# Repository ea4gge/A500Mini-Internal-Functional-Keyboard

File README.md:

# The A500Mini AmigaWave and RetroWiki's Internal Functional Keyboard Project

<br>

<br>

This is project of the A500Mini internal functional keyboard, based in 32U4 processor (Arduino leonardo, for example).

Actually it is working as final release, feel free to use, modify, recreate, ...

<br>

<br>

<br>

<br>

<br>

<br>

<br>

<br>

# The features:

1.- HID internal fully functional keyboard, with F12 key in the "eject" button of the disk drive, CAPS Lock led, ...

2.- Internal 4 USB's HUB: One for the keyboard, one for the SD reader, one internal free (for network, for example) tha last one for the rear original placed USB on the main unit (because one of the original populated USB must be used por the hub's imput)

3.- SD card's reader exactly in the floppy disk's place.

4.- A lot of smiles after the fabrication :D 

The readme file and the help file for the fabrication is WIP at the moment.

All the mechanical procedures are made by Kikems_Retro.

The presentation of the first prototype  (one weekend JOB) was in the youtube's AmigaWave program. We have also presented in the "Posadas party", in Spain 

The inspiration for my own code was from the "Armapad36v2" because is my firstt program of an USB Keyboard. Many thanks for the Author of this!!!

Spetial thanks to EA4EOZ. He has had the idea of use the Eject button and gave me a lot of help in the code of the Arduino

<br>

<br>

<br>

<br>

Many thanks to all and Enjoy!!

Lince// EA4GGE

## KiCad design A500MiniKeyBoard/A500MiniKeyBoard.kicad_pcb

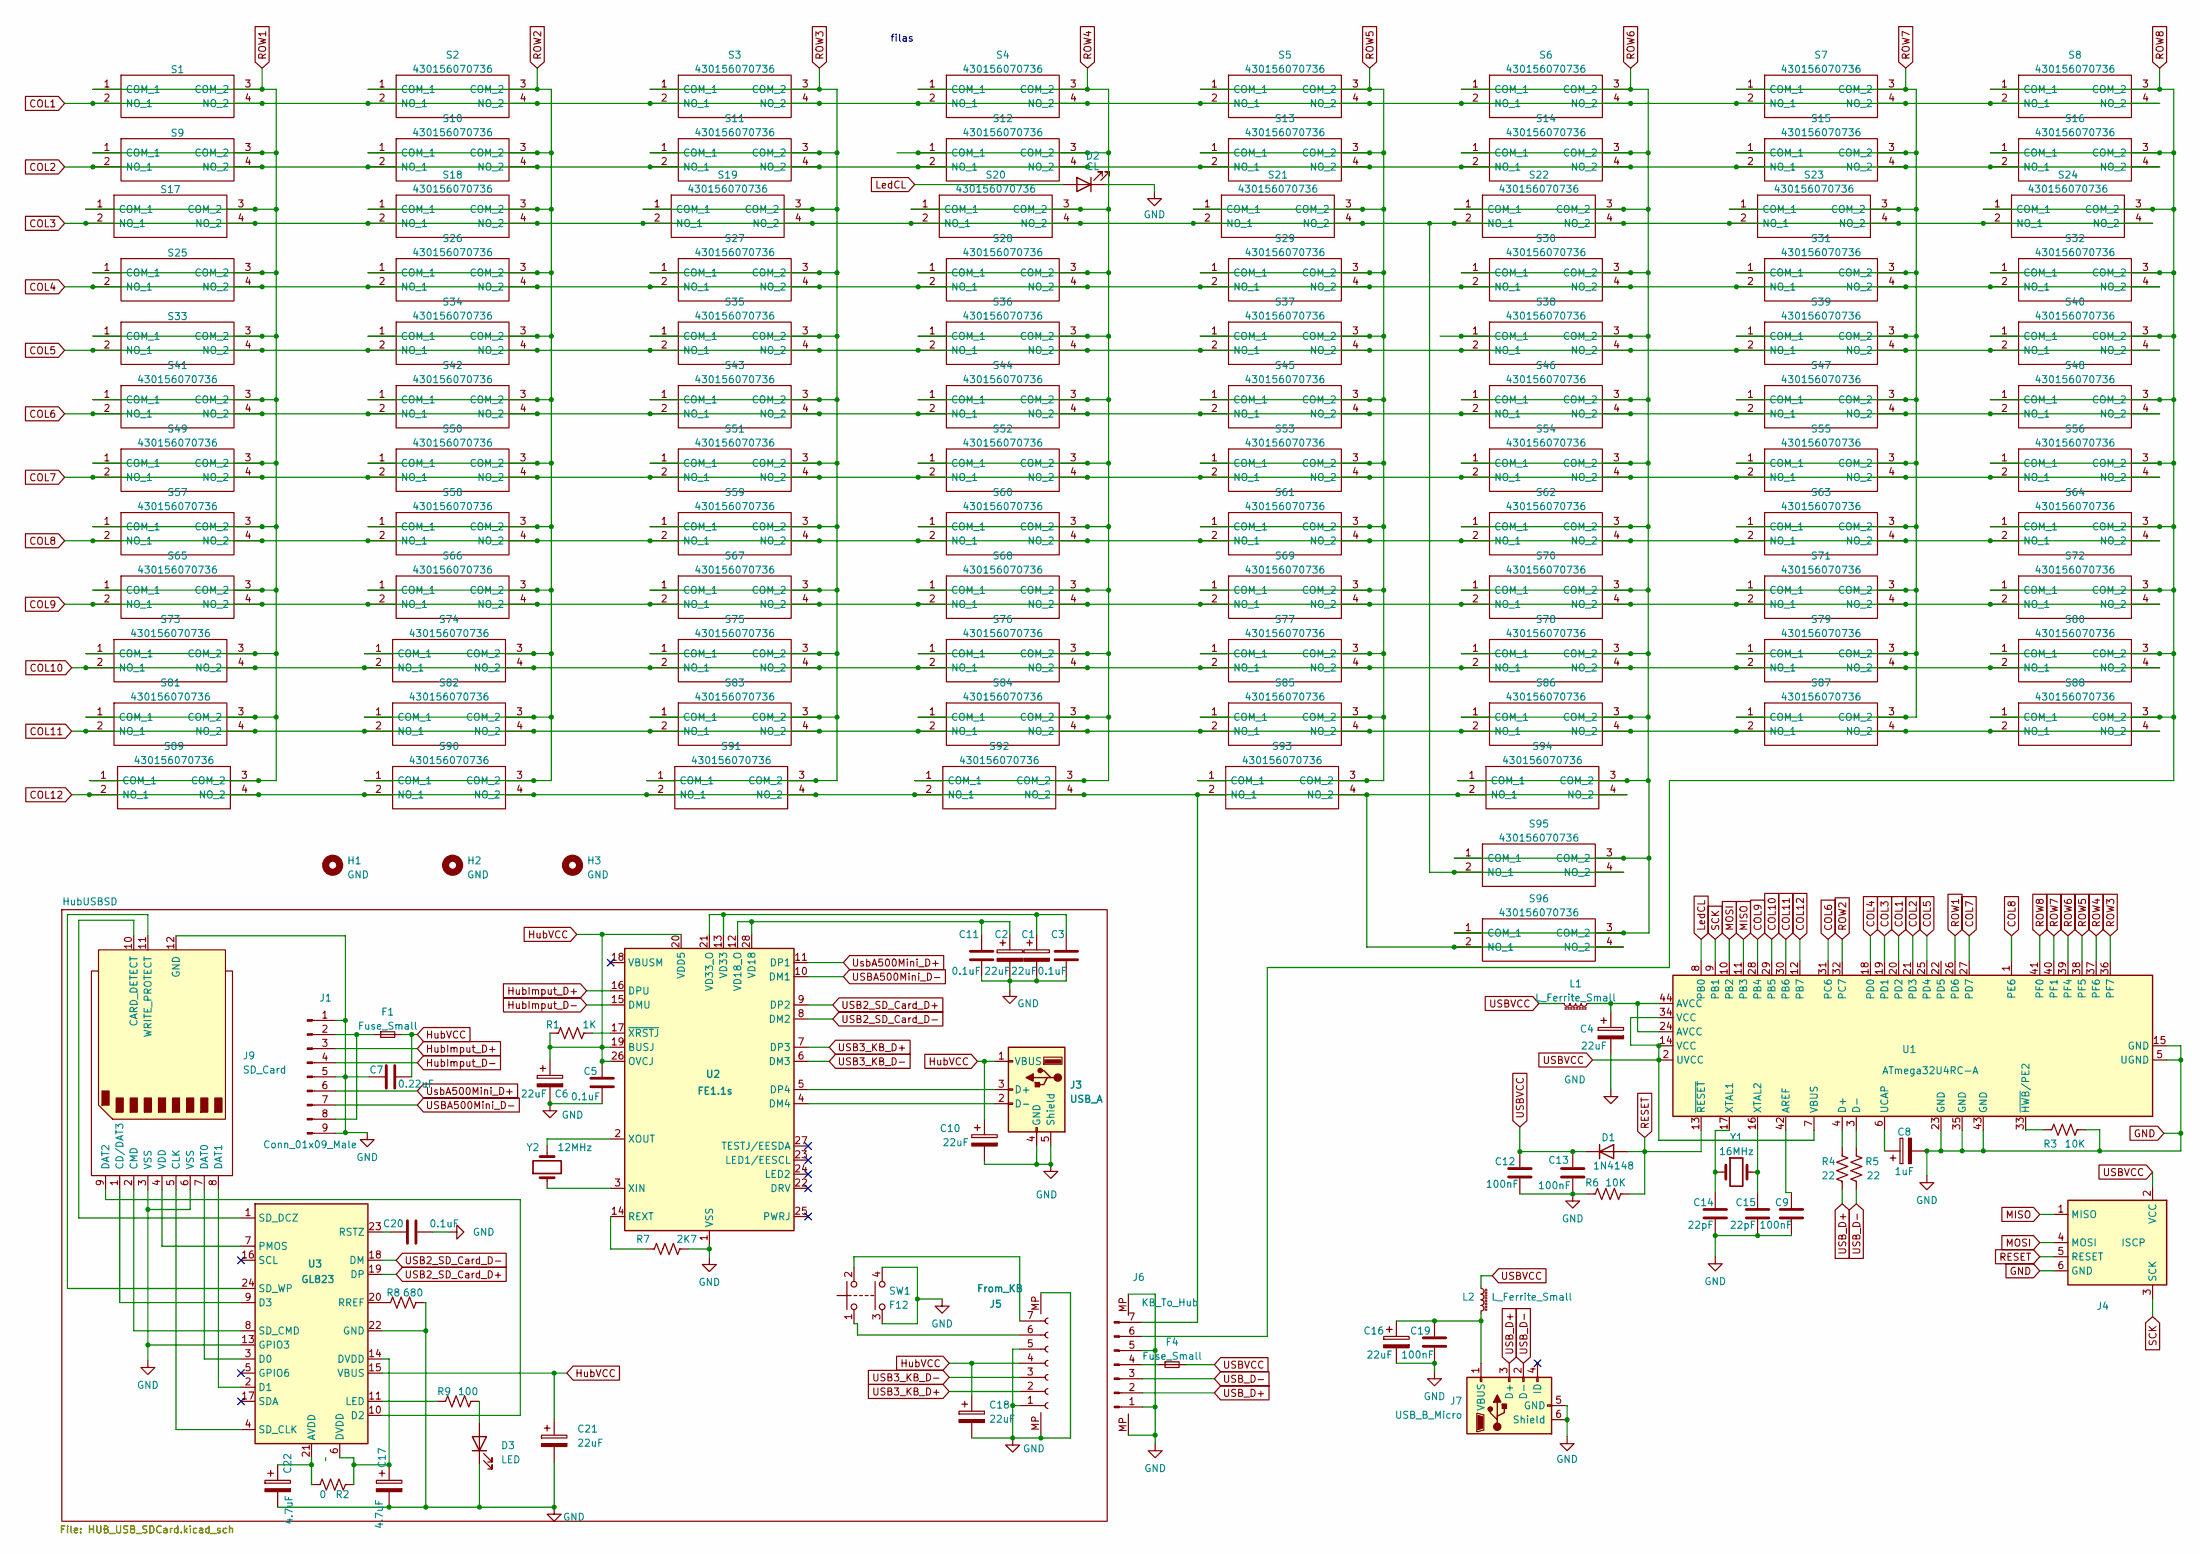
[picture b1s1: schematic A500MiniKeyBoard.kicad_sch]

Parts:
C1, C2, C4, C6, C10, C16, C18, C21: 22uF; CP_EIA-3528-21_Kemet-B_Pad1.50x2.35mm_HandSolder
C3, C5, C11, C20: 0.1uF; C_0805_2012Metric_Pad1.18x1.45mm_HandSolder
C7: 0.22uF; C_0805_2012Metric_Pad1.18x1.45mm_HandSolder
C8: 1uF; CP_EIA-3528-21_Kemet-B_Pad1.50x2.35mm_HandSolder
C9, C12, C13, C19: 100nF; C_0805_2012Metric_Pad1.18x1.45mm_HandSolder
C14, C15: 22pF; C_0805_2012Metric_Pad1.18x1.45mm_HandSolder
C17, C22: 4.7uF; CP_EIA-3528-21_Kemet-B_Pad1.50x2.35mm_HandSolder
D1: 1N4148; D_0805_2012Metric_Pad1.15x1.40mm_HandSolder
D2: CL; LED_0603_1608Metric
D3: LED; LED_D3.0mm_Horizontal_O1.27mm_Z2.0mm
F1, F4: Fuse_Small; Fuse_2920_7451Metric_Pad2.10x5.45mm_HandSolder
H1, H2, H3: GND; MountingHole_2.1mm
J1: Conn_01x09_Male; PinHeader_1x09_P2.54mm_Horizontal
J3: USB_A; USB_A_Molex_67643_Horizontal
J4: ISCP; PinHeader_2x03_P2.54mm_Vertical
J5: From_KB; TE_84953-7_1x07-1MP_P1.0mm_Horizontal
J6: KB_To_Hub; TE_84953-7_1x07-1MP_P1.0mm_Horizontal
J7: USB_B_Micro; USB_Micro-B_Amphenol_10118194_Horizontal
J9: SD_Card; SD_TE_2041021
L1, L2: L_Ferrite_Small; L_0805_2012Metric_Pad1.05x1.20mm_HandSolder
R1: 1K; R_0805_2012Metric_Pad1.20x1.40mm_HandSolder
R2: 0; R_0805_2012Metric_Pad1.20x1.40mm_HandSolder
R3, R6: 10K; R_0805_2012Metric_Pad1.20x1.40mm_HandSolder
R4, R5: 22; R_0805_2012Metric_Pad1.20x1.40mm_HandSolder
R7: 2K7; R_0805_2012Metric_Pad1.20x1.40mm_HandSolder
R8: 680; R_0805_2012Metric_Pad1.20x1.40mm_HandSolder
R9: 100; R_0805_2012Metric_Pad1.20x1.40mm_HandSolder
S1, S2, S3, S4, S5, S6, S7, S8, S9, S10, S11, S12, S13, S14, S15, S16, S17, S18, S19, S20, S21, S22, S23, S24, S25, S26, S27, S28, S29, S30, S31, S32, S33, S34, S35, S36, S37, S38, S39, S40, S41, S42, S43, S44, S45, S46, S47, S48, S49, S50, S51, S52, S53, S54, S55, S56, S57, S58, S59, S60, S61, S62, S63, S64, S65, S66, S67, S68, S69, S70, S71, S72, S73, S74, S75, S76, S77, S78, S79, S80, S81, S82, S83, S84, S85, S86, S87, S88, S89, S90, S91, S92, S93, S94, S95, S96: 430156070736; SW_PUSH_6mm_H7.3mm_mia; Mouser Part Number N/A
SW1: F12; SW_Tactile_SPST_Angled_PTS645Vx83-2LFS
U1: ATmega32U4RC-A; TQFP-44_10x10mm_P0.8mm
U2: FE1.1s; SSOP-28_3.9x9.9mm_P0.635mm
U3: GL823; SSOP-24_3.9x8.7mm_P0.635mm
Y1: 16MHz; Crystal_HC49-4H_Vertical
Y2: 12MHz; Crystal_HC49-4H_Vertical

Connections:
COL1: S1.2 (NO_1), S1.4 (NO_2), S2.2 (NO_1), S2.4 (NO_2), S3.2 (NO_1), S3.4 (NO_2), S4.2 (NO_1), S4.4 (NO_2), S5.2 (NO_1), S5.4 (NO_2), S6.2 (NO_1), S6.4 (NO_2), S7.2 (NO_1), S7.4 (NO_2), S8.2 (NO_1), S8.4 (NO_2), U1.20 (PD2)
COL2: S9.2 (NO_1), S9.4 (NO_2), S10.2 (NO_1), S10.4 (NO_2), S11.2 (NO_1), S11.4 (NO_2), S12.2 (NO_1), S12.4 (NO_2), S13.2 (NO_1), S13.4 (NO_2), S14.2 (NO_1), S14.4 (NO_2), S15.2 (NO_1), S15.4 (NO_2), S16.2 (NO_1), S16.4 (NO_2), U1.21 (PD3)
COL3: S17.2 (NO_1), S17.4 (NO_2), S18.2 (NO_1), S18.4 (NO_2), S19.2 (NO_1), S19.4 (NO_2), S20.2 (NO_1), S20.4 (NO_2), S21.2 (NO_1), S21.4 (NO_2), S22.2 (NO_1), S22.4 (NO_2), S23.2 (NO_1), S23.4 (NO_2), S24.2 (NO_1), S24.4 (NO_2), S95.2 (NO_1), S95.4 (NO_2), U1.19 (PD1)
COL4: S25.2 (NO_1), S25.4 (NO_2), S26.2 (NO_1), S26.4 (NO_2), S27.2 (NO_1), S27.4 (NO_2), S28.2 (NO_1), S28.4 (NO_2), S29.2 (NO_1), S29.4 (NO_2), S30.2 (NO_1), S30.4 (NO_2), S31.2 (NO_1), S31.4 (NO_2), S32.2 (NO_1), S32.4 (NO_2), U1.18 (PD0)
COL5: S33.2 (NO_1), S33.4 (NO_2), S34.2 (NO_1), S34.4 (NO_2), S35.2 (NO_1), S35.4 (NO_2), S36.2 (NO_1), S36.4 (NO_2), S37.2 (NO_1), S37.4 (NO_2), S38.2 (NO_1), S38.4 (NO_2), S39.2 (NO_1), S39.4 (NO_2), S40.2 (NO_1), S40.4 (NO_2), U1.25 (PD4)
COL6: S41.2 (NO_1), S41.4 (NO_2), S42.2 (NO_1), S42.4 (NO_2), S43.2 (NO_1), S43.4 (NO_2), S44.2 (NO_1), S44.4 (NO_2), S45.2 (NO_1), S45.4 (NO_2), S46.2 (NO_1), S46.4 (NO_2), S47.2 (NO_1), S47.4 (NO_2), S48.2 (NO_1), S48.4 (NO_2), U1.31 (PC6)
COL7: S49.2 (NO_1), S49.4 (NO_2), S50.2 (NO_1), S50.4 (NO_2), S51.2 (NO_1), S51.4 (NO_2), S52.2 (NO_1), S52.4 (NO_2), S53.2 (NO_1), S53.4 (NO_2), S54.2 (NO_1), S54.4 (NO_2), S55.2 (NO_1), S55.4 (NO_2), S56.2 (NO_1), S56.4 (NO_2), U1.27 (PD7)
COL8: S57.2 (NO_1), S57.4 (NO_2), S58.2 (NO_1), S58.4 (NO_2), S59.2 (NO_1), S59.4 (NO_2), S60.2 (NO_1), S60.4 (NO_2), S61.2 (NO_1), S61.4 (NO_2), S62.2 (NO_1), S62.4 (NO_2), S63.2 (NO_1), S63.4 (NO_2), S64.2 (NO_1), S64.4 (NO_2), U1.1 (PE6)
COL9: S65.2 (NO_1), S65.4 (NO_2), S66.2 (NO_1), S66.4 (NO_2), S67.2 (NO_1), S67.4 (NO_2), S68.2 (NO_1), S68.4 (NO_2), S69.2 (NO_1), S69.4 (NO_2), S70.2 (NO_1), S70.4 (NO_2), S71.2 (NO_1), S71.4 (NO_2), S72.2 (NO_1), S72.4 (NO_2), U1.28 (PB4)
COL10: S73.2 (NO_1), S73.4 (NO_2), S74.2 (NO_1), S74.4 (NO_2), S75.2 (NO_1), S75.4 (NO_2), S76.2 (NO_1), S76.4 (NO_2), S77.2 (NO_1), S77.4 (NO_2), S78.2 (NO_1), S78.4 (NO_2), S79.2 (NO_1), S79.4 (NO_2), S80.2 (NO_1), S80.4 (NO_2), U1.29 (PB5)
COL11: S81.2 (NO_1), S81.4 (NO_2), S82.2 (NO_1), S82.4 (NO_2), S83.2 (NO_1), S83.4 (NO_2), S84.2 (NO_1), S84.4 (NO_2), S85.2 (NO_1), S85.4 (NO_2), S86.2 (NO_1), S86.4 (NO_2), S87.2 (NO_1), S87.4 (NO_2), S88.2 (NO_1), S88.4 (NO_2), U1.30 (PB6)
COL12: J6.7, S89.2 (NO_1), S89.4 (NO_2), S90.2 (NO_1), S90.4 (NO_2), S91.2 (NO_1), S91.4 (NO_2), S92.2 (NO_1), S92.4 (NO_2), S93.2 (NO_1), S93.4 (NO_2), S94.2 (NO_1), S94.4 (NO_2), S96.2 (NO_1), S96.4 (NO_2), U1.12 (PB7)
GND: C1.2, C2.2, C3.1, C4.2, C5.1, C6.2, C7.1, C8.2, C9.2, C10.2, C11.2, C12.1, C13.1, C14.2, C15.2, C16.2, C17.2, C18.2, C19.1, C20.1, C21.2, C22.2, D2.1 (K), D3.1 (K), J1.1, J1.5, J1.9, J3.4 (GND), J3.5 (Shield), J4.6 (GND), J5.1, J5.5, J5.MP, J6.1, J6.5, J6.MP, J7.5 (GND), J7.6 (Shield), J9.3 (VSS), J9.6 (VSS), J9.12 (GND), R3.2, R6.1, R7.1, R8.1, SW1.3, SW1.4, U1.5 (UGND), U1.15 (GND), U1.23 (GND), U1.35 (GND), U1.43 (GND), U2.1 (VSS), U3.13 (GPIO3), U3.22 (GND)
HubImput_D+: J1.3, U2.16 (DPU)
HubImput_D-: J1.4, U2.15 (DMU)
HubVCC: C5.2, C6.1, C7.2, C10.1, C18.1, C21.1, F1.2, J3.1 (VBUS), J5.4, R1.2, U2.19 (BUSJ), U2.20 (VDD5), U2.26 (OVCJ), U3.15 (VBUS)
LedCL: D2.2 (A), U1.8 (PB0)
MISO: J4.1 (MISO), U1.11 (PB3)
MOSI: J4.4 (MOSI), U1.10 (PB2)
unnamed: C4.1, L1.1, U1.24 (AVCC), U1.44 (AVCC)
unnamed: C17.1, R2.2, U3.6 (DVDD), U3.14 (DVDD)
unnamed: D3.2 (A), R9.1
unnamed: F1.1, J1.2, J1.8
unnamed: J3.3 (D+), U2.5 (DP4)
unnamed: J3.2 (D-), U2.4 (DM4)
unnamed: J5.6, SW1.1
unnamed: J5.7, SW1.2
unnamed: F4.1, J6.4
unnamed: C16.1, C19.2, J7.1 (VBUS), L2.2
unnamed: J9.10 (CARD_DETECT), U3.1 (SD_DCZ)
unnamed: J9.1 (CD/DAT3), U3.9 (D3)
unnamed: J9.5 (CLK), U3.4 (SD_CLK)
unnamed: J9.2 (CMD), U3.8 (SD_CMD)
unnamed: J9.7 (DAT0), U3.3 (D0)
unnamed: J9.8 (DAT1), U3.2 (D1)
unnamed: J9.9 (DAT2), U3.10 (D2)
unnamed: J9.4 (VDD), U3.7 (PMOS)
unnamed: J9.11 (WRITE_PROTECT), U3.24 (SD_WP)
unnamed: C9.1, U1.42 (AREF)
unnamed: R4.1, U1.4 (D+)
unnamed: R5.1, U1.3 (D-)
unnamed: C8.1, U1.6 (UCAP)
unnamed: C14.1, U1.17 (XTAL1), Y1.1
unnamed: C15.1, U1.16 (XTAL2), Y1.2
unnamed: R3.1, U1.33 (~HWB/PE2)
unnamed: R7.2, U2.14 (REXT)
unnamed: C2.1, C11.1, U2.12 (VD18_O), U2.28 (VD18)
unnamed: C1.1, C3.2, U2.13 (VD33), U2.21 (VD33_O)
unnamed: U2.3 (XIN), Y2.1
unnamed: U2.2 (XOUT), Y2.2
unnamed: R1.1, U2.17 (~XRSTJ)
unnamed: C22.1, R2.1, U3.21 (AVDD)
unnamed: R9.2, U3.11 (LED)
unnamed: R8.2, U3.20 (RREF)
unnamed: C20.2, U3.23 (RSTZ)
RESET: D1.2 (A), J4.5 (RESET), R6.2, U1.13 (~RESET)
ROW1: S1.1 (COM_1), S1.3 (COM_2), S9.1 (COM_1), S9.3 (COM_2), S17.1 (COM_1), S17.3 (COM_2), S25.1 (COM_1), S25.3 (COM_2), S33.1 (COM_1), S33.3 (COM_2), S41.1 (COM_1), S41.3 (COM_2), S49.1 (COM_1), S49.3 (COM_2), S57.1 (COM_1), S57.3 (COM_2), S65.1 (COM_1), S65.3 (COM_2), S73.1 (COM_1), S73.3 (COM_2), S81.1 (COM_1), S81.3 (COM_2), S89.1 (COM_1), S89.3 (COM_2), U1.26 (PD6)
ROW2: S2.1 (COM_1), S2.3 (COM_2), S10.1 (COM_1), S10.3 (COM_2), S18.1 (COM_1), S18.3 (COM_2), S26.1 (COM_1), S26.3 (COM_2), S34.1 (COM_1), S34.3 (COM_2), S42.1 (COM_1), S42.3 (COM_2), S50.1 (COM_1), S50.3 (COM_2), S58.1 (COM_1), S58.3 (COM_2), S66.1 (COM_1), S66.3 (COM_2), S74.1 (COM_1), S74.3 (COM_2), S82.1 (COM_1), S82.3 (COM_2), S90.1 (COM_1), S90.3 (COM_2), U1.32 (PC7)
ROW3: S3.1 (COM_1), S3.3 (COM_2), S11.1 (COM_1), S11.3 (COM_2), S19.1 (COM_1), S19.3 (COM_2), S27.1 (COM_1), S27.3 (COM_2), S35.1 (COM_1), S35.3 (COM_2), S43.1 (COM_1), S43.3 (COM_2), S51.1 (COM_1), S51.3 (COM_2), S59.1 (COM_1), S59.3 (COM_2), S67.1 (COM_1), S67.3 (COM_2), S75.1 (COM_1), S75.3 (COM_2), S83.1 (COM_1), S83.3 (COM_2), S91.1 (COM_1), S91.3 (COM_2), U1.36 (PF7)
ROW4: S4.1 (COM_1), S4.3 (COM_2), S12.1 (COM_1), S12.3 (COM_2), S20.1 (COM_1), S20.3 (COM_2), S28.1 (COM_1), S28.3 (COM_2), S36.1 (COM_1), S36.3 (COM_2), S44.1 (COM_1), S44.3 (COM_2), S52.1 (COM_1), S52.3 (COM_2), S60.1 (COM_1), S60.3 (COM_2), S68.1 (COM_1), S68.3 (COM_2), S76.1 (COM_1), S76.3 (COM_2), S84.1 (COM_1), S84.3 (COM_2), S92.1 (COM_1), S92.3 (COM_2), U1.37 (PF6)
ROW5: S5.1 (COM_1), S5.3 (COM_2), S13.1 (COM_1), S13.3 (COM_2), S21.1 (COM_1), S21.3 (COM_2), S29.1 (COM_1), S29.3 (COM_2), S37.1 (COM_1), S37.3 (COM_2), S45.1 (COM_1), S45.3 (COM_2), S53.1 (COM_1), S53.3 (COM_2), S61.1 (COM_1), S61.3 (COM_2), S69.1 (COM_1), S69.3 (COM_2), S77.1 (COM_1), S77.3 (COM_2), S85.1 (COM_1), S85.3 (COM_2), S93.1 (COM_1), S93.3 (COM_2), U1.38 (PF5)
ROW6: S6.1 (COM_1), S6.3 (COM_2), S14.1 (COM_1), S14.3 (COM_2), S22.1 (COM_1), S22.3 (COM_2), S30.1 (COM_1), S30.3 (COM_2), S38.1 (COM_1), S38.3 (COM_2), S46.1 (COM_1), S46.3 (COM_2), S54.1 (COM_1), S54.3 (COM_2), S62.1 (COM_1), S62.3 (COM_2), S70.1 (COM_1), S70.3 (COM_2), S78.1 (COM_1), S78.3 (COM_2), S86.1 (COM_1), S86.3 (COM_2), S94.1 (COM_1), S94.3 (COM_2), S95.1 (COM_1), S95.3 (COM_2), S96.1 (COM_1), S96.3 (COM_2), U1.39 (PF4)
ROW7: S7.1 (COM_1), S7.3 (COM_2), S15.1 (COM_1), S15.3 (COM_2), S23.1 (COM_1), S23.3 (COM_2), S31.1 (COM_1), S31.3 (COM_2), S39.1 (COM_1), S39.3 (COM_2), S47.1 (COM_1), S47.3 (COM_2), S55.1 (COM_1), S55.3 (COM_2), S63.1 (COM_1), S63.3 (COM_2), S71.1 (COM_1), S71.3 (COM_2), S79.1 (COM_1), S79.3 (COM_2), S87.1 (COM_1), S87.3 (COM_2), U1.40 (PF1)
ROW8: J6.6, S8.1 (COM_1), S8.3 (COM_2), S16.1 (COM_1), S16.3 (COM_2), S24.1 (COM_1), S24.3 (COM_2), S32.1 (COM_1), S32.3 (COM_2), S40.1 (COM_1), S40.3 (COM_2), S48.1 (COM_1), S48.3 (COM_2), S56.1 (COM_1), S56.3 (COM_2), S64.1 (COM_1), S64.3 (COM_2), S72.1 (COM_1), S72.3 (COM_2), S80.1 (COM_1), S80.3 (COM_2), S88.1 (COM_1), S88.3 (COM_2), U1.41 (PF0)
SCK: J4.3 (SCK), U1.9 (PB1)
USB2_SD_Card_D+: U2.9 (DP2), U3.19 (DP)
USB2_SD_Card_D-: U2.8 (DM2), U3.18 (DM)
USB3_KB_D+: J5.2, U2.7 (DP3)
USB3_KB_D-: J5.3, U2.6 (DM3)
USBA500Mini_D-: J1.7, U2.10 (DM1)
USBVCC: C12.2, C13.2, D1.1 (K), F4.2, J4.2 (VCC), L1.2, L2.1, U1.2 (UVCC), U1.7 (VBUS), U1.14 (VCC), U1.34 (VCC)
USB_D+: J6.2, J7.3 (D+), R4.2
USB_D-: J6.3, J7.2 (D-), R5.2
UsbA500Mini_D+: J1.6, U2.11 (DP1)

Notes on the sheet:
filas

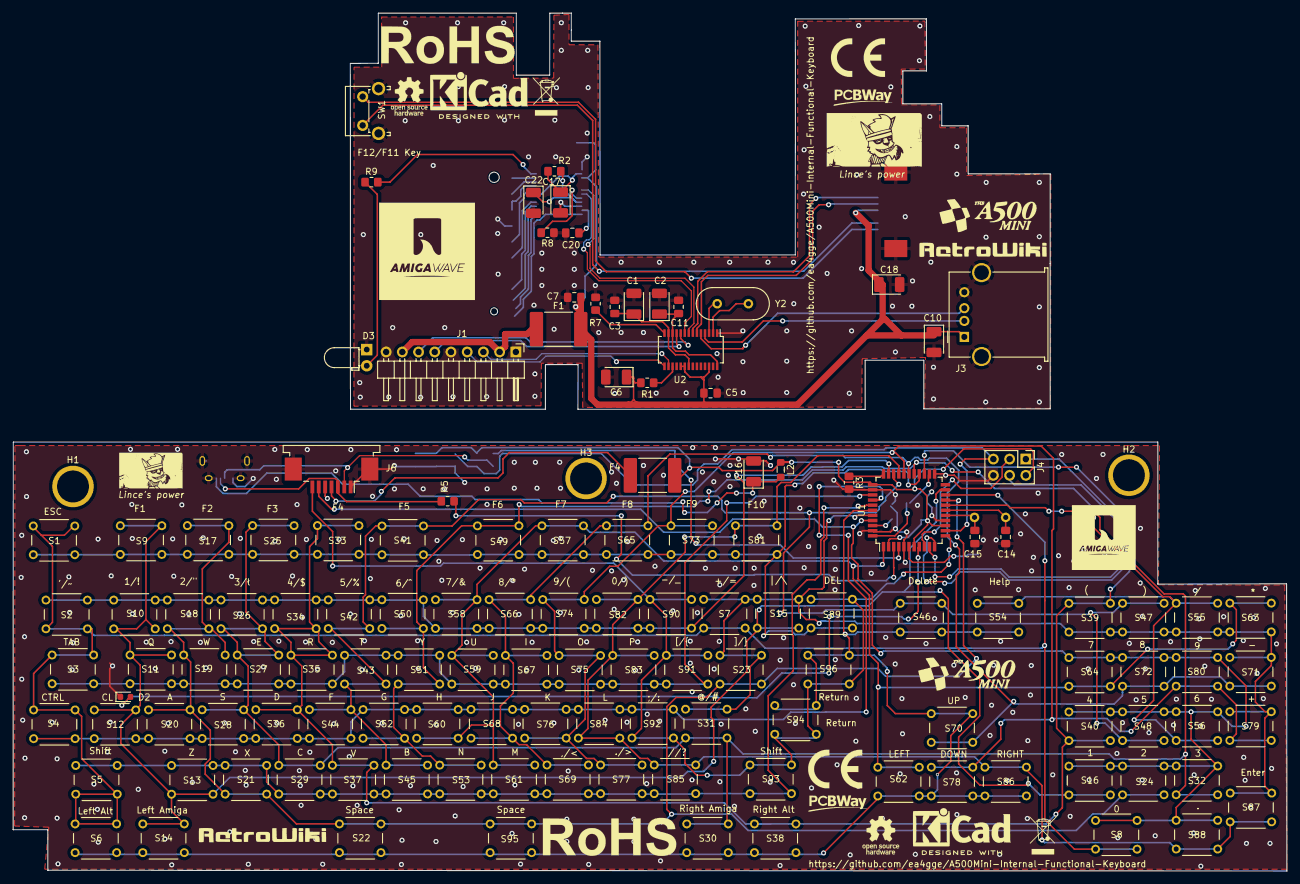
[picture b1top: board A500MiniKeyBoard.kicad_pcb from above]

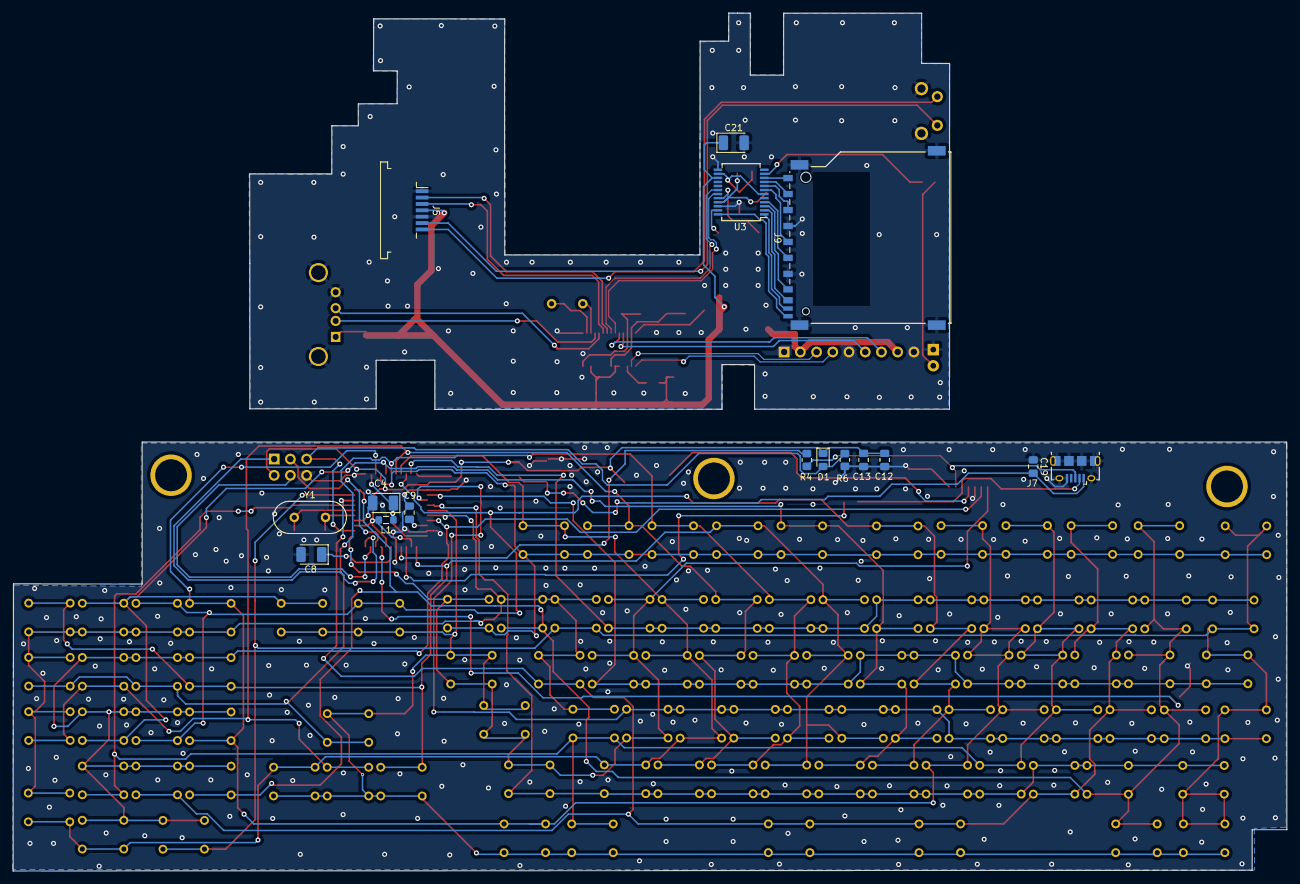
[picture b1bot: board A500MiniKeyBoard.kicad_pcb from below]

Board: 2 copper layers, 199.5 x 134.4 mm, 166 parts (16 on the bottom side), 74 nets.

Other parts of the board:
G6, G13: LOGO; pcbway_10X3_3
G7: LOGO; Logo_Lince_15X8
G8, G10: LOGO; theA500Mini_16_9X16_9
G9: LOGO; Logo_Lince_10X6
REF1, REF11: RoHS-Logo_6mm_SilkScreen
REF2, REF15: KiCad-Logo2_6mm_SilkScreen
REF3, REF14: OSHW-Logo_5.7x6mm_SilkScreen
REF4, REF16: WEEE-Logo_4.2x6mm_SilkScreen
REF5, REF12: CE-Logo_8.5x6mm_SilkScreen

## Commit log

2022-05-17 Add files via upload
    Arduino code for A500MiniKeyb
2022-05-23 Add files via upload
    Keyboard with the Issues "multiple keys" and "keyPad" solved. Old is in the .Bak file
2022-05-23 Update README.md
    Solved the ISSUES with the layout
2022-05-23 Update A500Mini_Keyboard.ino
    Older in the A500Mini_Keyboard's directory, in the .bak file. Here the latest update
